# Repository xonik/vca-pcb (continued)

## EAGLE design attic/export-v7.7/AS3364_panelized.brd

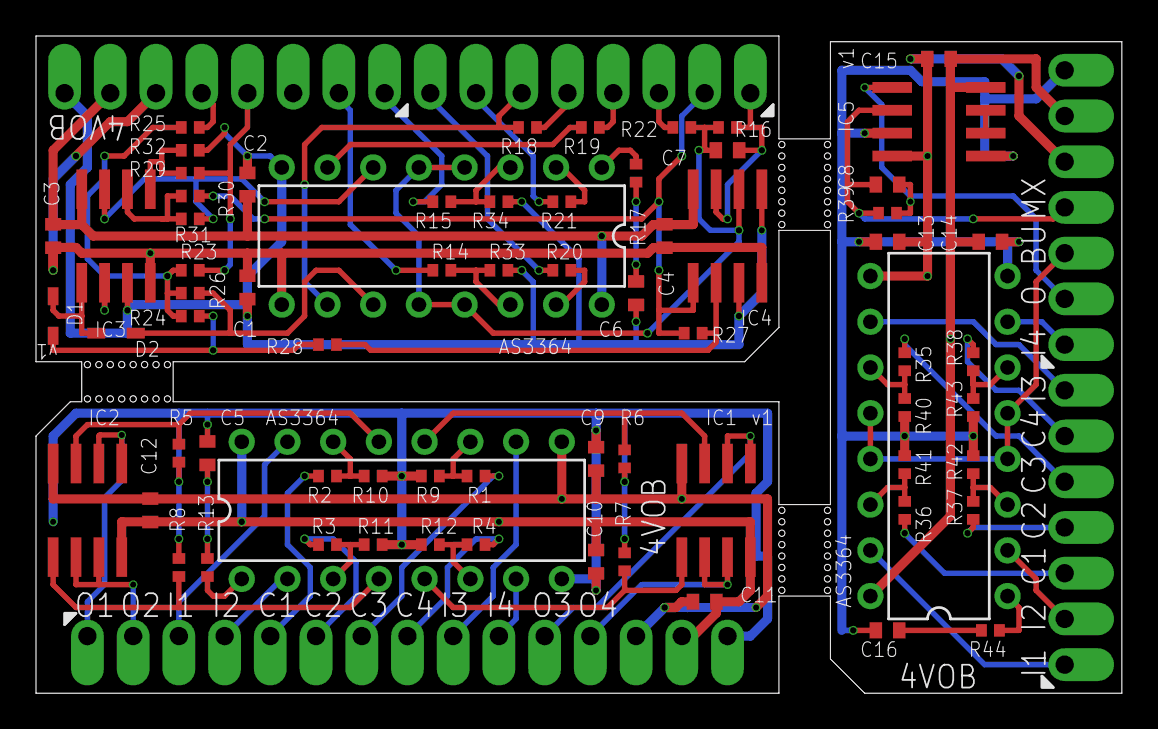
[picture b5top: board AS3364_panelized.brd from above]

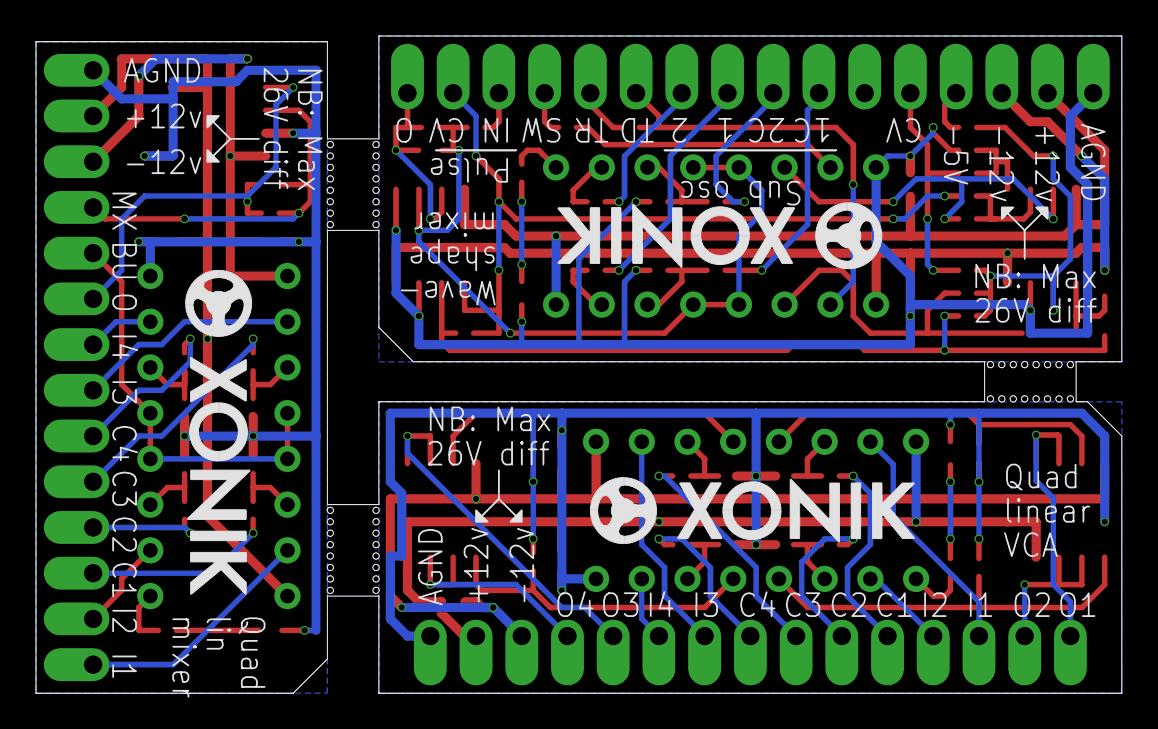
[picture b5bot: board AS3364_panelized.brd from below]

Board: 2 copper layers, 60.3 x 36.5 mm, 78 parts (3 on the bottom side), 77 nets.

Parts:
C1, C2, C3, C4, C9, C10, C11, C12, C13, C14, C15: 100nF; C0402
C5, C6, C16: 5nF; C0402
C7, C8: 33pF; C0402
D1, D2: SOD323J
DA1, DA2, DA3: AS3364D; DIL16J
IC1, IC2, IC3, IC4, IC5: TL072JD; SO08J
R1, R2, R3, R4, R14, R15, R35, R36, R37, R38: 33k; R0402
R5, R6, R7, R8, R16, R18, R19, R20, R21, R22, R39: 47k; R0402
R9, R10, R11, R12, R33, R34, R40, R41, R42, R43: 22k; R0402
R13, R17, R44: 100R; R0402
R23, R27, R29, R30: 25k; R0402
R24, R26, R31, R32: 20k; R0402
R25: 50k; R0402
R28: 10k; R0402
SV1: SIP-PIN15-1J
SV2, SV3: SIP-PIN08-1J
U$1, U$2, U$3: XONIK_LOGO_18
U$4, U$5: MA07-1JP; SIP-PIN07-1J

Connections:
+12V: C10.2, C11.2, C12.2, DA2.16, IC1.8, IC2.8, SV1.14
+12V1: C2.2, C3.2, C4.2, DA1.16, IC3.8, IC4.8, SV3.7
+12V2: C14.2, C15.2, DA3.16, IC5.8, U$4.6
-5V: R25.1, SV3.5
-12V: C9.1, C11.1, C12.1, DA2.9, IC1.4, IC2.4, SV1.13
-12V1: C1.1, C3.1, C4.1, DA1.9, IC3.4, IC4.4, SV3.6
-12V2: C13.1, C15.1, DA3.9, IC5.4, U$4.5
BUS: DA3.4, DA3.5, DA3.12, DA3.13, U$4.3
CV1: R2.1, SV1.5
CV2: R3.1, SV1.6
CV2_IN: DA2.3, R3.2, R11.2
CV2_IN1: DA3.3, R37.2, R42.2
CV3: R1.1, SV1.7
CV4: R4.1, SV1.8
CV5: R36.1, U$5.3
CV6: R35.1, U$5.5
CV7: R38.1, U$5.6
CV8: R37.1, U$5.4
GND: C5.1, C9.2, C10.1, DA2.8, R5.1, R6.1, R7.1, R8.1, R9.1, R10.1, R11.1, R12.1, SV1.15
GND1: C1.2, C2.1, C6.1, DA1.8, IC3.3, IC4.3, IC4.5, R32.1, R33.1, R34.1, SV3.8
GND2: C13.2, C14.1, C16.1, DA3.8, IC5.3, IC5.5, R40.1, R41.1, R42.1, R43.1, U$4.7
IN1: DA2.15, SV1.3
IN2: DA2.2, SV1.4
IN3: DA2.10, SV1.9
IN4: DA2.7, SV1.10
IN5: DA3.10, U$5.7
IN6: DA3.7, U$4.1
IN7: DA3.2, U$5.2
IN8: DA3.15, U$5.1
MIX: C8.1, IC5.2, R39.1, U$4.4
MIX_BUS: C7.2, DA1.4, DA1.5, DA1.12, DA1.13, IC4.6, R16.2, R22.1
unnamed: DA1.1, R17.2
unnamed: DA2.1, R13.2
unnamed: C6.2, R17.1
unnamed: DA2.4, IC2.5, R8.2
unnamed: IC3.5, R29.2, R32.2
unnamed: DA2.5, IC1.5, R7.2
unnamed: D1.1, D2.2, IC3.1
unnamed: IC3.2, R23.2, R24.1, R25.2, R26.1
unnamed: DA3.1, R44.2
unnamed: DA2.6, R4.2, R12.2
unnamed: DA2.12, IC1.3, R6.2
unnamed: DA2.11, R1.2, R9.2
unnamed: DA2.13, IC2.3, R5.2
unnamed: C5.2, R13.1
unnamed: IC3.6, R30.2, R31.1
unnamed: DA3.6, R38.2, R43.2
unnamed: DA3.11, R35.2, R40.2
unnamed: IC4.2, R27.1, R28.2
unnamed: D1.2, R24.2, R28.1
unnamed: DA3.14, R36.2, R41.2
unnamed: DA2.14, R2.2, R10.2
unnamed: C16.2, R44.1
NC1: IC5.6, IC5.7
OUT: C7.1, IC4.7, R16.1, SV2.1
OUT1: IC2.1, IC2.2, SV1.1
OUT2: IC2.6, IC2.7, SV1.2
OUT3: IC1.1, IC1.2, SV1.11
OUT4: IC1.6, IC1.7, SV1.12
OUT5: C8.2, IC5.1, R39.2, U$4.2
PAN_CV: R23.1, R29.1, SV3.4
PULSE_CV: IC4.1, R27.2, R30.1, SV2.2
PULSE_IN: R22.2, SV2.3
SAW: R19.1, SV2.4
SAW_CV: DA1.6, IC3.7, R31.2
SAW_IN: DA1.7, R19.2
SUB1: R20.1, SV2.8
SUB1_CV: R14.1, SV3.2
SUB1_CV_IN: DA1.14, R14.2, R33.2
SUB1_IN: DA1.15, R20.2
SUB2: R21.1, SV2.7
SUB2_CV: R15.1, SV3.1
SUB2_CV_IN: DA1.3, R15.2, R34.2
SUB2_IN: DA1.2, R21.2
TRI: R18.1, SV2.5
TRI_CV: D2.1, DA1.11, R26.2
TRI_IN: DA1.10, R18.2, SV2.6

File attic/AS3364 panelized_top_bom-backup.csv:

Comment,Designator,Footprint,LCSC Part #
5nF,C5 C6 C16,C0402,C1538
1N4148,D1 D2,SOD323J,C2128
10k,R28,R0402,C25744
20k,R24 R26 R31 R32,R0402,C25765
22k,R9 R10 R11 R12 R33 R34 R40 R41 R42 R43,R0402,C25768
25k,R23 R27 R29 R30,R0402,C25874
33k,R1 R2 R3 R4 R14 R15 R35 R36 R37 R38,R0402,C25779
33pF,C7 C8,C0402,C1562
47k,R5 R6 R7 R8 R16 R18 R19 R20 R21 R22 R39,R0402,C25792
50k,R25,R0402,C25897
100R,R13 R17 R44,R0402,C25076
100nF,C1 C2 C3 C4 C9 C10 C11 C12 C13 C14 C15,C0402,C307331
TL072,IC1 IC2 IC3 IC4 IC5,SO08,C6961
AS3364D,DA1 DA2 DA3,DIL16J,C72130

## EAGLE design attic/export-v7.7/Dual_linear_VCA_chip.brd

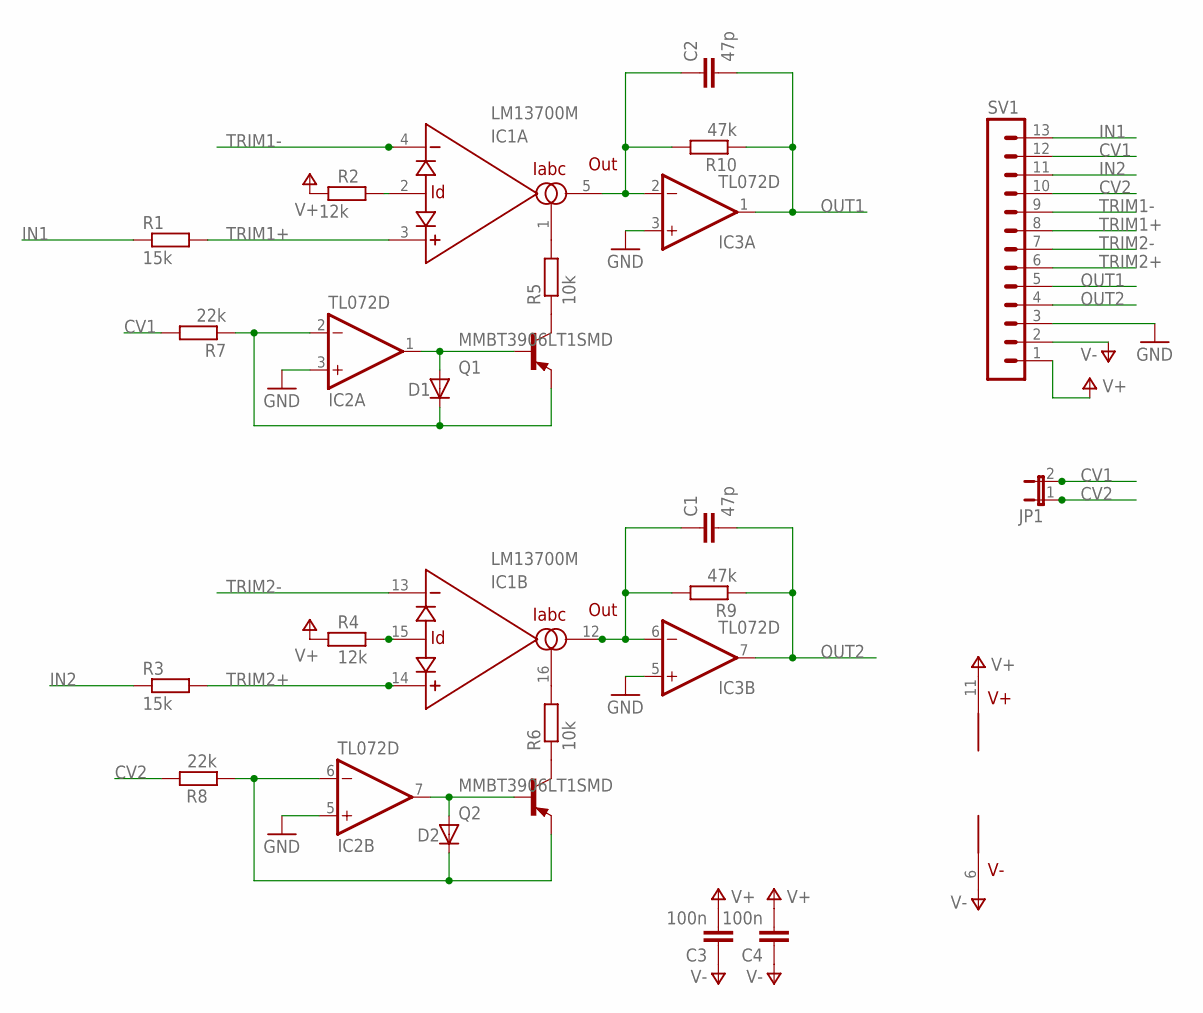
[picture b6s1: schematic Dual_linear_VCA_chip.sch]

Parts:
C1, C2: 47p; C0805
C3, C4: 100n; C0805
D1, D2: DIODE-SOD80C; SOD80C
IC1: LM13700M; SO16
IC2, IC3: TL072D; SO08
JP1: JP1E; JP1
Q1, Q2: MMBT3906LT1SMD; SOT23-BEC
R1, R3: 15k; R0805
R2, R4: 12k; R0805
R5, R6: 10k; R0805
R7, R8: 22k; R0805
R9, R10: 47k; R0805
SV1: MA13-1

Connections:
CV1: JP1.2, R7.2, SV1.12
CV2: JP1.1, R8.2, SV1.10
GND: IC2.3 (+IN), IC2.5 (+IN), IC3.3 (+IN), IC3.5 (+IN), SV1.3
IN1: R1.1, SV1.13
IN2: R3.1, SV1.11
unnamed: Q1.C, R5.1
unnamed: Q2.C, R6.1
unnamed: D1.C, IC2.2 (-IN), Q1.E, R7.1
unnamed: IC1.1 (IABC), R5.2
unnamed: IC1.2 (ID), R2.2
unnamed: D2.A, IC2.7 (OUT), Q2.B
unnamed: C2.1, IC1.5 (OUT), IC3.2 (-IN), R10.2
unnamed: D1.A, IC2.1 (OUT), Q1.B
unnamed: D2.C, IC2.6 (-IN), Q2.E, R8.1
unnamed: IC1.16 (IABC), R6.2
unnamed: IC1.15 (ID), R4.2
unnamed: C1.1, IC1.12 (OUT), IC3.6 (-IN), R9.2
OUT1: C2.2, IC3.1 (OUT), R10.1, SV1.4
OUT2: C1.2, IC3.7 (OUT), R9.1, SV1.5
TRIM1+: IC1.3 (+IN), R1.2, SV1.8
TRIM1-: IC1.4 (-IN), SV1.9
TRIM2+: IC1.14 (+IN), R3.2, SV1.6
TRIM2-: IC1.13 (-IN), SV1.7
V+: C3.2, C4.2, IC1.11 (V+), IC2.8 (V+), IC3.8 (V+), R2.1, R4.1, SV1.1
V-: C3.1, C4.1, IC1.6 (V-), IC2.4 (V-), IC3.4 (V-), SV1.2

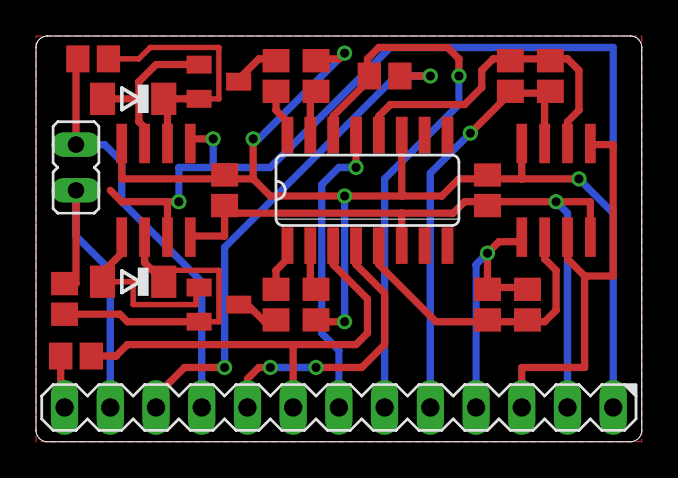
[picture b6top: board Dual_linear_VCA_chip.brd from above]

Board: 2 copper layers, 33.7 x 22.5 mm, 23 parts (0 on the bottom side), 25 nets.

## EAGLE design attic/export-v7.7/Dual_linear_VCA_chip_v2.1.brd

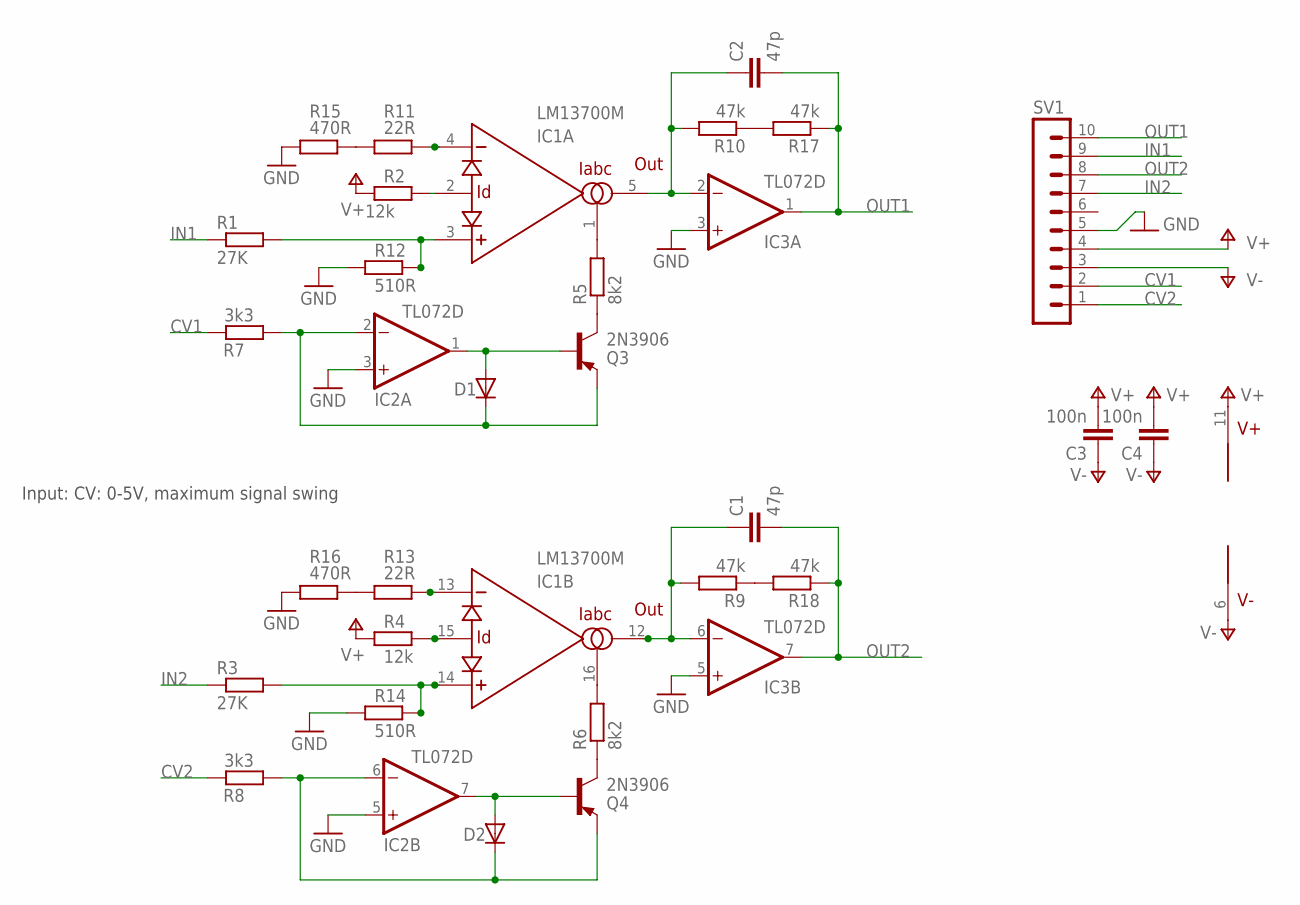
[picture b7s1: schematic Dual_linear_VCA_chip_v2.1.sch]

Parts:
C1, C2: 47p; C0805
C3, C4: 100n; C0805
D1, D2: DIODE-SOD80C; SOD80C
IC1: LM13700M; SO16
IC2, IC3: TL072D; SO08
Q3, Q4: 2N3906; TO92
R1, R3: 27K; R0805
R2, R4: 12k; R0805
R5, R6: 8k2; R0805
R7, R8: 3k3; R0805
R9, R10, R17, R18: 47k; R0805
R11, R13: 22R; R0805
R12, R14: 510R; R0805
R15, R16: 470R; R0805
SV1: MA10-1

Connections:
CV1: R7.2, SV1.2
CV2: R8.2, SV1.1
GND: IC2.3 (+IN), IC2.5 (+IN), IC3.3 (+IN), IC3.5 (+IN), R12.1, R14.1, R15.1, R16.1, SV1.5
IN1: R1.1, SV1.9
IN2: R3.1, SV1.7
unnamed: Q3.1 (C), R5.1
unnamed: Q4.1 (C), R6.1
unnamed: D1.C, IC2.2 (-IN), Q3.3 (E), R7.1
unnamed: IC1.1 (IABC), R5.2
unnamed: R11.1, R15.2
unnamed: IC1.2 (ID), R2.2
unnamed: R13.1, R16.2
unnamed: D2.A, IC2.7 (OUT), Q4.2 (B)
unnamed: C2.1, IC1.5 (OUT), IC3.2 (-IN), R10.2
unnamed: D1.A, IC2.1 (OUT), Q3.2 (B)
unnamed: D2.C, IC2.6 (-IN), Q4.3 (E), R8.1
unnamed: R10.1, R17.2
unnamed: IC1.16 (IABC), R6.2
unnamed: R9.1, R18.2
unnamed: IC1.15 (ID), R4.2
unnamed: C1.1, IC1.12 (OUT), IC3.6 (-IN), R9.2
OUT1: C2.2, IC3.1 (OUT), R17.1, SV1.10
OUT2: C1.2, IC3.7 (OUT), R18.1, SV1.8
TRIM1+: IC1.3 (+IN), R1.2, R12.2
TRIM1-: IC1.4 (-IN), R11.2
TRIM2+: IC1.14 (+IN), R3.2, R14.2
TRIM2-: IC1.13 (-IN), R13.2
V+: C3.2, C4.2, IC1.11 (V+), IC2.8 (V+), IC3.8 (V+), R2.1, R4.1, SV1.4
V-: C3.1, C4.1, IC1.6 (V-), IC2.4 (V-), IC3.4 (V-), SV1.3

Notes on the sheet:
Input: CV: 0-5V, maximum signal swing

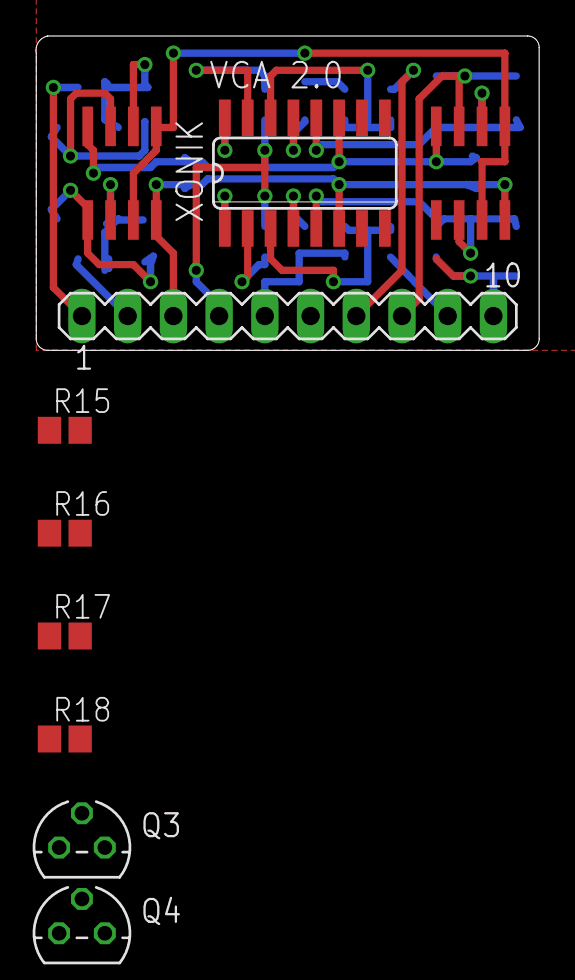
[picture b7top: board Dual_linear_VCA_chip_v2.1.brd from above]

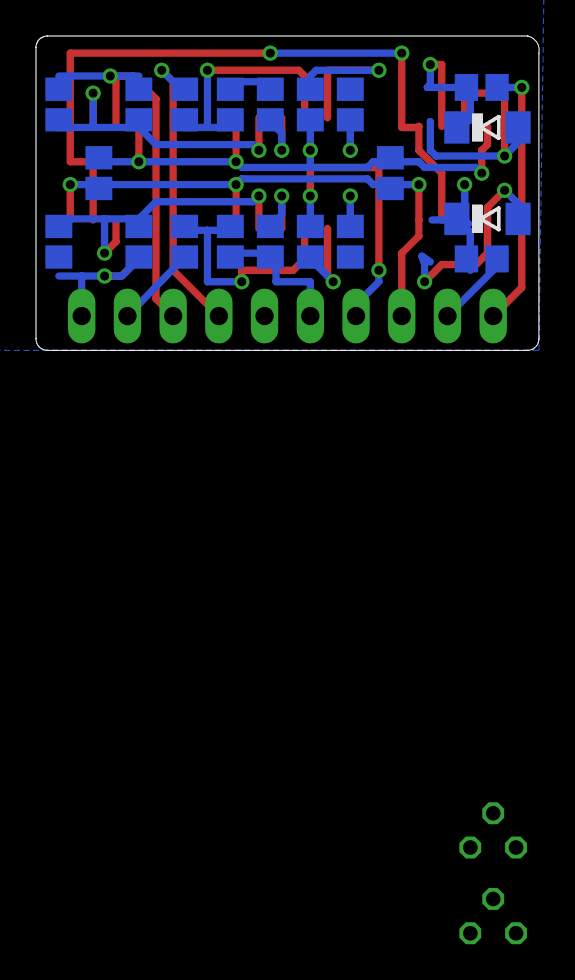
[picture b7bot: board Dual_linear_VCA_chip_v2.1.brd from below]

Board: 2 copper layers, 28.0 x 17.5 mm, 30 parts (20 on the bottom side), 29 nets.
